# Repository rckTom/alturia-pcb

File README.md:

# Alturia PCB

This repository contains all data to build the hardware of the Alturia rocket flight computer. 

## Features
-  STM32F303CC CPU (48Kb Ram, 256Kb internal Flash)
-  MS5607 Barometric pressure sensor
-  BMI088 IMU (Acceleration: +-24g, rotational rate: +-2000°/s)
-  AIS2120SXTR high acceleration sensor (+-120g)
-  64 Megabyte external flash for logging and configuration data
-  Reverse polarity protection
-  4 x Pyro output channels with max 25A current
-  2 x PWM connector for servos
-  USB (CDC-ACM, Mass Storage and DFU)

## Getting Started

The board is built with [Kicad](http://kicad.org/). Version 5.2 or newer is required. The firmware is located at [alturia-firmware](https://github.com/rckTom/alturia-firmware)

## Board Versions
*   v1.0 rev.B *Initial Board Design*
*   v1.1 rev.A *Fix wrongly connected Crystal*
*   v1.1 rev.B *Fix swaped Pins of the speaker mosfet*

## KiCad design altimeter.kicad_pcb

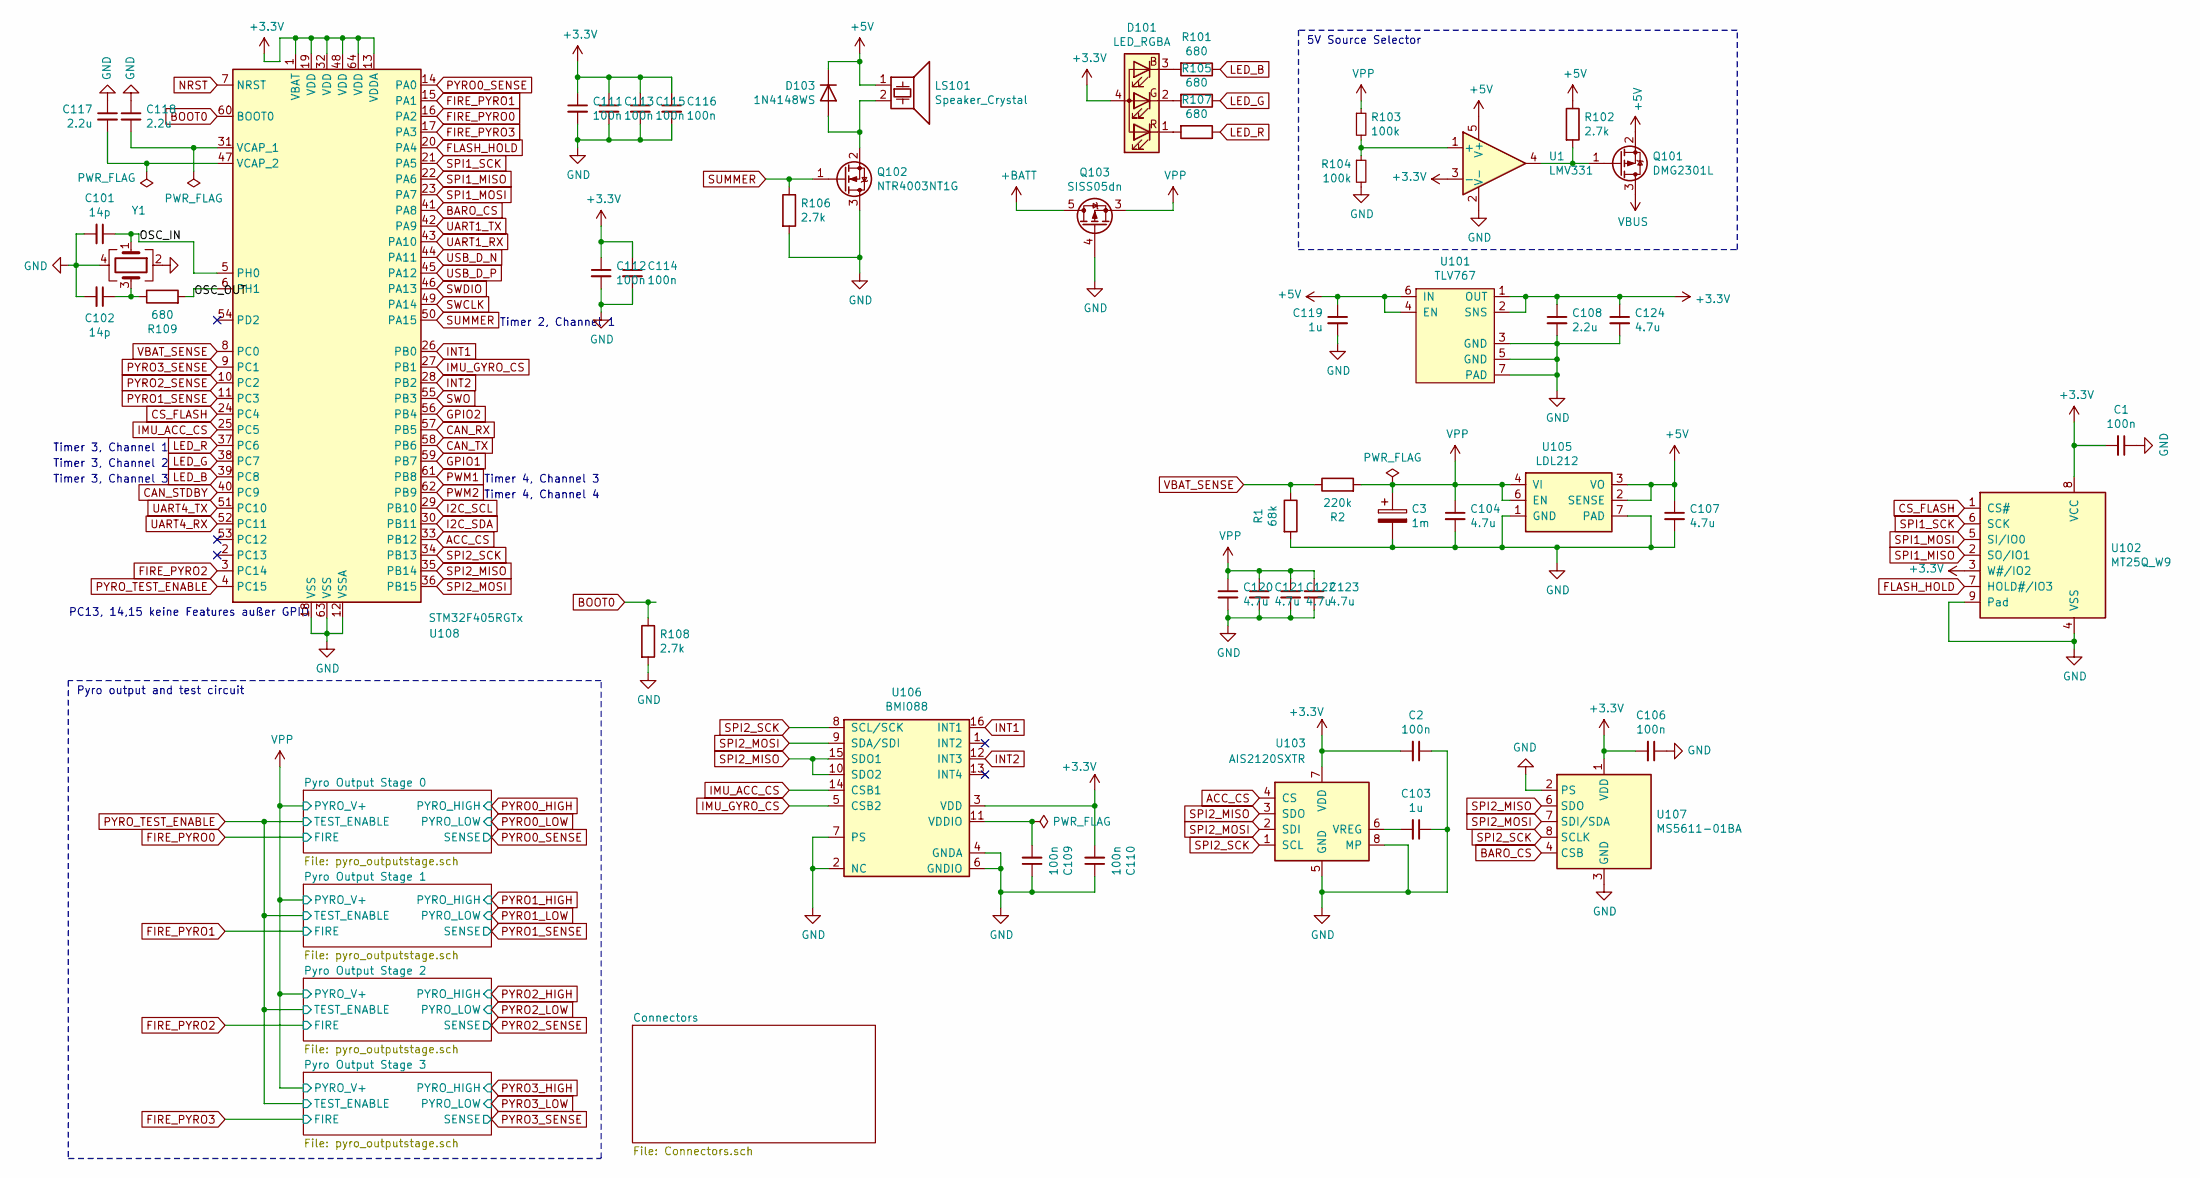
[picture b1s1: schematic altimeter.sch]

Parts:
C1, C2, C106, C109, C110, C111, C112, C113, C114, C115, C116: 100n; C_0402_1005Metric
C3: 1m; CP_Axial_L11.0mm_D8.0mm_P15.00mm_Horizontal
C101, C102: 14p; C_0402_1005Metric
C103: 1u; C_0603_1608Metric_Pad1.05x0.95mm_HandSolder
C104, C120, C121, C122, C123: 4.7u; C_0805_2012Metric_Pad1.15x1.40mm_HandSolder
C107: 4.7u; C_0805_2012Metric
C108: 2.2u; C_0603_1608Metric_Pad1.05x0.95mm_HandSolder
C117, C118: 2.2u; C_0402_1005Metric
C119: 1u; C_0805_2012Metric
C124: 4.7u; C_0603_1608Metric_Pad1.05x0.95mm_HandSolder
D101: LED_RGBA; SMD_RGB_LED
D103: 1N4148WS; D_SOD-323
LS101: Speaker_Crystal; CSS-95B30-SMT
Q101: DMG2301L; SOT-23
Q102: NTR4003NT1G; SOT-23
Q103: SISS05dn; Vishay_PowerPAK_1212-8_Single
R1: 68k; R_0402_1005Metric
R2: 220k; R_0402_1005Metric
R101, R105, R107, R109: 680; R_0402_1005Metric
R102, R106, R108: 2.7k; R_0402_1005Metric
R103, R104: 100k; R_0402_1005Metric
U1: LMV331; SOT-353_SC-70-5
U101: TLV767; TI_WSON_TLV767
U102: MT25Q_W9; micron-wpdfn_8x6mm
U103: AIS2120SXTR; SOIC-8_3.9x4.9mm_P1.27mm
U105: LDL212; DFN-6-1EP_3x3mm_P0.95mm_EP1.7x2.6mm
U106: BMI088
U107: MS5611-01BA; LGA-8_3x5mm_P1.25mm
U108: STM32F405RGTx; LQFP-64_10x10mm_P0.5mm
Y1: Crystal_GND24; Crystal_SMD_2016-4Pin_2.0x1.6mm

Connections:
+3V3: C1.2, C2.2, C106.2, C108.1, C110.2, C111.1, C112.1, C113.1, C114.1, C115.1, C116.1, C124.1, D101.4 (A), U1.3 (-), U101.1 (OUT), U101.2 (SNS), U102.3 (W#/IO2), U102.8 (VCC), U103.7 (VDD), U106.3 (VDD), U107.1 (VDD), U108.1 (VBAT), U108.13 (VDDA), U108.19 (VDD), U108.32 (VDD), U108.48 (VDD), U108.64 (VDD); also elsewhere on the board
+5V: C107.1, C119.1, D103.1 (K), LS101.1, Q101.2 (S), R102.1, U1.5 (V+), U101.4 (EN), U101.6 (IN), U105.2 (SENSE), U105.3 (VO); also elsewhere on the board
+BATT: Q103.5 (D); also elsewhere on the board
/OSC_IN: C101.1, U108.5 (PH0), Y1.1
/OSC_OUT: R109.2, U108.6 (PH1)
ACC_CS: U103.4 (CS), U108.33 (PB12)
BARO_CS: U107.4 (CSB), U107.5 (CSB), U108.41 (PA8)
BOOT0: R108.1, U108.60 (BOOT0)
CAN_RX: U108.57 (PB5); also elsewhere on the board
CAN_STDBY: U108.40 (PC9); also elsewhere on the board
CAN_TX: U108.58 (PB6); also elsewhere on the board
CS_FLASH: U102.1 (CS#), U108.24 (PC4)
FIRE_PYRO2: U108.3 (PC14); also elsewhere on the board
FIRE_PYRO3: U108.17 (PA3); also elsewhere on the board
FLASH_HOLD: U102.7 (HOLD#/IO3), U108.20 (PA4)
GND: C1.1, C2.1, C3.2, C101.2, C102.2, C103.1, C104.2, C106.1, C107.2, C108.2, C109.1, C110.1, C111.2, C112.2, C113.2, C114.2, C115.2, C116.2, C117.1, C118.1, C119.2, C120.2, C121.2, C122.2, C123.2, C124.2, Q102.3 (D), Q103.4 (G), R1.2, R104.2, R106.2, R108.2, U1.2 (V-), U101.3 (GND), U101.5 (GND), U101.7 (PAD), U102.4 (VSS), U102.9 (Pad), U103.5 (GND), U103.8 (MP), U105.1 (GND), U105.7 (PAD), U106.2 (NC), U106.4 (GNDA), U106.6 (GNDIO), U106.7 (PS), U107.2 (PS), U107.3 (GND), U108.12 (VSSA), U108.18 (VSS), U108.63 (VSS), Y1.2, Y1.4; also elsewhere on the board
GPIO1: U108.59 (PB7); also elsewhere on the board
GPIO2: U108.56 (PB4); also elsewhere on the board
I2C_SCL: U108.29 (PB10); also elsewhere on the board
I2C_SDA: U108.30 (PB11); also elsewhere on the board
IMU_ACC_CS: U106.14 (CSB1), U108.25 (PC5)
IMU_GYRO_CS: U106.5 (CSB2), U108.27 (PB1)
INT1: U106.16 (INT1), U108.26 (PB0)
INT2: U106.12 (INT3), U108.28 (PB2)
LED_B: R101.1, U108.39 (PC8)
LED_G: R105.1, U108.38 (PC7)
LED_R: R107.1, U108.37 (PC6)
NRST: U108.7 (NRST); also elsewhere on the board
unnamed: C102.1, R109.1, Y1.3
unnamed: C103.2, U103.6 (VREG)
unnamed: C109.2, U106.11 (VDDIO)
unnamed: C117.2, U108.47 (VCAP_2)
unnamed: C118.2, U108.31 (VCAP_1)
unnamed: D101.1 (RK), R107.2
unnamed: D101.2 (GK), R105.2
unnamed: D101.3 (BK), R101.2
unnamed: D103.2 (A), LS101.2, Q102.2 (S)
unnamed: Q101.1 (G), R102.2, U1.4
unnamed: R103.2, R104.1, U1.1 (+)
PWM1: U108.61 (PB8); also elsewhere on the board
PWM2: U108.62 (PB9); also elsewhere on the board
PYRO0_SENSE: U108.14 (PA0); also elsewhere on the board
PYRO1_SENSE: U108.11 (PC3); also elsewhere on the board
PYRO2_SENSE: U108.10 (PC2); also elsewhere on the board
PYRO3_SENSE: U108.9 (PC1); also elsewhere on the board
PYRO_TEST_ENABLE: U108.4 (PC15); also elsewhere on the board
SPI1_MISO: U102.2 (SO/IO1), U108.22 (PA6)
SPI1_MOSI: U102.5 (SI/IO0), U108.23 (PA7)
SPI1_SCK: U102.6 (SCK), U108.21 (PA5)
SPI2_MISO: U103.3 (SDO), U106.10 (SDO2), U106.15 (SDO1), U107.6 (SDO), U108.35 (PB14)
SPI2_MOSI: U103.2 (SDI), U106.9 (SDA/SDI), U107.7 (SDI/SDA), U108.36 (PB15)
SPI2_SCK: U103.1 (SCL), U106.8 (SCL/SCK), U107.8 (SCLK), U108.34 (PB13)
SUMMER: Q102.1 (G), R106.1, U108.50 (PA15)
SWCLK: U108.49 (PA14); also elsewhere on the board
SWDIO: U108.46 (PA13); also elsewhere on the board
SWO: U108.55 (PB3); also elsewhere on the board
UART1_RX: U108.43 (PA10); also elsewhere on the board
UART1_TX: U108.42 (PA9); also elsewhere on the board
UART4_RX: U108.52 (PC11); also elsewhere on the board
UART4_TX: U108.51 (PC10); also elsewhere on the board
USB_D_N: U108.44 (PA11); also elsewhere on the board
USB_D_P: U108.45 (PA12); also elsewhere on the board
VBAT_SENSE: R1.1, R2.1, U108.8 (PC0)
VBUS: Q101.3 (D); also elsewhere on the board

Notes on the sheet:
Pyro output and test circuit
5V Source Selector
Timer 4, Channel 4
Timer 4, Channel 3
Timer 3, Channel 1
Timer 3, Channel 2
Timer 3, Channel 3
Timer 2, Channel 1
PC13, 14,15 keine Features außer GPIO

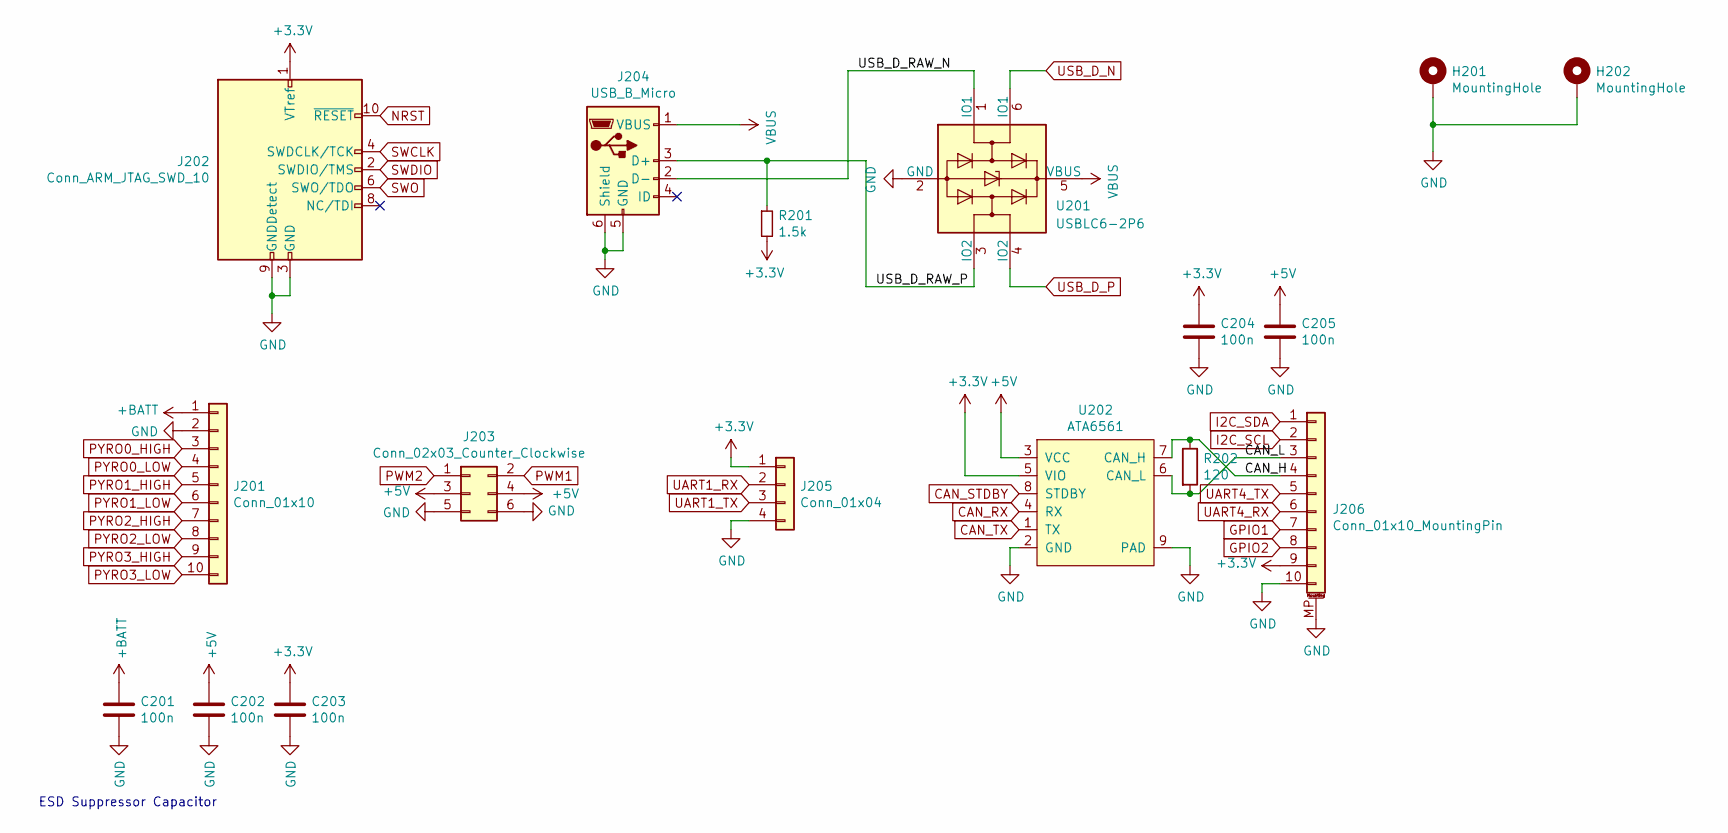
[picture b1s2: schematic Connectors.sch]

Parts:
C201, C202, C203, C204, C205: 100n; C_0402_1005Metric
H201, H202: MountingHole; MountingHole_3.2mm_M3_Pad_Via
J201: Conn_01x10; Molex_MicroClasp_55935-1010_1x10_P2.00mm_Horizontal
J202: Conn_ARM_JTAG_SWD_10; PinHeader_2x05_P2.00mm_Vertical_SMD
J203: Conn_02x03_Counter_Clockwise; PinHeader_2x03_P2.54mm_Horizontal
J204: USB_B_Micro; USB_Micro-B_Molex-105017-0001
J205: Conn_01x04; Molex_PicoBlade_53048-0410_1x04_P1.25mm_Horizontal
J206: Conn_01x10_MountingPin; Molex_PicoBlade_53398-1071_1x10-1MP_P1.25mm_Vertical
R201: 1.5k; R_0402_1005Metric
R202: 120; R_0603_1608Metric_Pad1.05x0.95mm_HandSolder
U201: USBLC6-2P6; SOT-666
U202: ATA6561; DFN-8-1EP_3x3mm_P0.65mm_EP1.55x2.4mm

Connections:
+3V3: C203.1, C204.1, J202.1 (VTref), J205.1, J206.9, R201.2, U202.5 (VIO); also elsewhere on the board
+5V: C202.1, C205.1, J203.3, J203.4, U202.3 (VCC); also elsewhere on the board
+BATT: C201.1, J201.1; also elsewhere on the board
/Connectors/CAN_H: J206.4, R202.1, U202.7 (CAN_H)
/Connectors/CAN_L: J206.3, R202.2, U202.6 (CAN_L)
/Connectors/USB_D_RAW_N: J204.2 (D-), U201.1 (IO1)
/Connectors/USB_D_RAW_P: J204.3 (D+), R201.1, U201.3 (IO2)
CAN_RX: U202.4 (RX); also elsewhere on the board
CAN_STDBY: U202.8 (STDBY); also elsewhere on the board
CAN_TX: U202.1 (TX); also elsewhere on the board
GND: C201.2, C202.2, C203.2, C204.2, C205.2, H201.1, H202.1, J201.2, J202.3 (GND), J202.5 (GND), J202.9 (GNDDetect), J203.5, J203.6, J204.5 (GND), J204.6 (Shield), J205.4, J206.10, J206.MP (MountPin), U201.2 (GND), U202.2 (GND), U202.9 (PAD); also elsewhere on the board
GPIO1: J206.7; also elsewhere on the board
GPIO2: J206.8; also elsewhere on the board
I2C_SCL: J206.2; also elsewhere on the board
I2C_SDA: J206.1; also elsewhere on the board
NRST: J202.10 (~RESET~); also elsewhere on the board
PWM1: J203.2; also elsewhere on the board
PWM2: J203.1; also elsewhere on the board
PYRO2_LOW: J201.8; also elsewhere on the board
PYRO3_LOW: J201.10; also elsewhere on the board
SWCLK: J202.4 (SWDCLK/TCK); also elsewhere on the board
SWDIO: J202.2 (SWDIO/TMS); also elsewhere on the board
SWO: J202.6 (SWO/TDO); also elsewhere on the board
UART1_RX: J205.2; also elsewhere on the board
UART1_TX: J205.3; also elsewhere on the board
UART4_RX: J206.6; also elsewhere on the board
UART4_TX: J206.5; also elsewhere on the board
USB_D_N: U201.6 (IO1); also elsewhere on the board
USB_D_P: U201.4 (IO2); also elsewhere on the board
VBUS: J204.1 (VBUS), U201.5 (VBUS); also elsewhere on the board

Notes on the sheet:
ESD Suppressor Capacitor

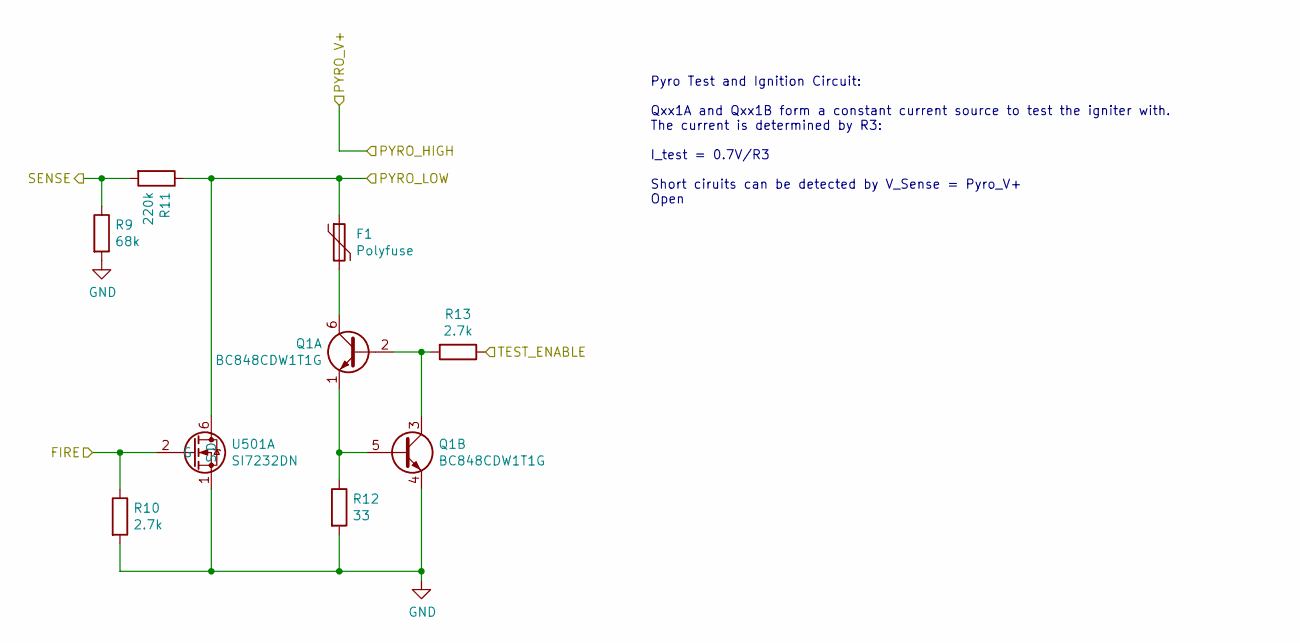
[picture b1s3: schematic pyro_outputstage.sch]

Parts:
F301: Polyfuse; Fuse_0603_1608Metric_Pad1.05x0.95mm_HandSolder
Q301: BC848CDW1T1G; SOT-363_SC-70-6
R3: 68k; R_0402_1005Metric
R4: 220k; R_0402_1005Metric
R301, R303: 2.7k; R_0402_1005Metric
R302: 33; R_0402_1005Metric
U301: SI7232DN; Vishay_PowerPAK_1212-8_Dual

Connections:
GND: Q301.4 (E2), R3.2, R301.2, R302.2, U301.1 (S), U301.3 (S); also elsewhere on the board
unnamed: F301.2, Q301.6 (C1)
unnamed: Q301.1 (E1), Q301.5 (B2), R302.1
unnamed: Q301.2 (B1), Q301.3 (C2), R303.2
PYRO0_SENSE: R3.1, R4.2; also elsewhere on the board
PYRO_TEST_ENABLE: R303.1; also elsewhere on the board

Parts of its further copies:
F1, F401, F501: Polyfuse; Fuse_0603_1608Metric_Pad1.05x0.95mm_HandSolder
Q1, Q401, Q501: BC848CDW1T1G; SOT-363_SC-70-6
R5, R7, R9: 68k; R_0402_1005Metric
R6, R8, R11: 220k; R_0402_1005Metric
R10, R13, R401, R403, R501, R503: 2.7k; R_0402_1005Metric
R12, R402, R502: 33; R_0402_1005Metric
U501: SI7232DN; Vishay_PowerPAK_1212-8_Dual

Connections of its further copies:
FIRE_PYRO2: R501.1, U501.4 (G); also elsewhere on the board
FIRE_PYRO3: R10.1, U501.2 (G); also elsewhere on the board
GND: Q1.4 (E2), Q401.4 (E2), Q501.4 (E2), R5.2, R7.2, R9.2, R10.2, R12.2, R401.2, R402.2, R501.2, R502.2, U501.1 (S), U501.3 (S); also elsewhere on the board
unnamed: F1.2, Q1.6 (C1)
unnamed: F401.2, Q401.6 (C1)
unnamed: F501.2, Q501.6 (C1)
unnamed: Q1.1 (E1), Q1.5 (B2), R12.1
unnamed: Q1.2 (B1), Q1.3 (C2), R13.2
unnamed: Q401.1 (E1), Q401.5 (B2), R402.1
unnamed: Q401.2 (B1), Q401.3 (C2), R403.2
unnamed: Q501.1 (E1), Q501.5 (B2), R502.1
unnamed: Q501.2 (B1), Q501.3 (C2), R503.2
PYRO1_SENSE: R5.1, R6.2; also elsewhere on the board
PYRO2_LOW: F501.1, R8.1, U501.5 (D); also elsewhere on the board
PYRO2_SENSE: R7.1, R8.2; also elsewhere on the board
PYRO3_LOW: F1.1, R11.1, U501.6 (D); also elsewhere on the board
PYRO3_SENSE: R9.1, R11.2; also elsewhere on the board
PYRO_TEST_ENABLE: R13.1, R403.1, R503.1; also elsewhere on the board

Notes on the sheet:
Pyro Test and Ignition Circuit: Qxx1A and Qxx1B form a constant current source to test the igniter with. The current is determined by R3: I_test = 0.7V/R3 Short ciruits can be detected by V_Sense = Pyro_V+ Open

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
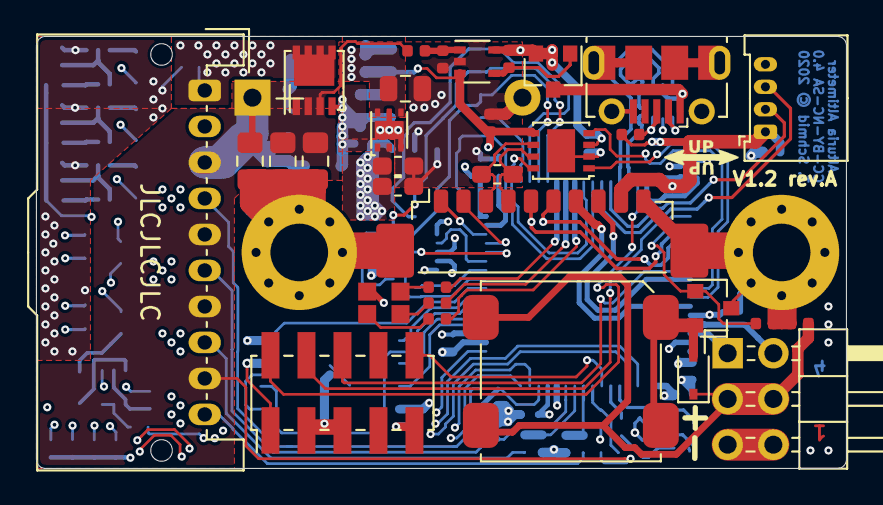
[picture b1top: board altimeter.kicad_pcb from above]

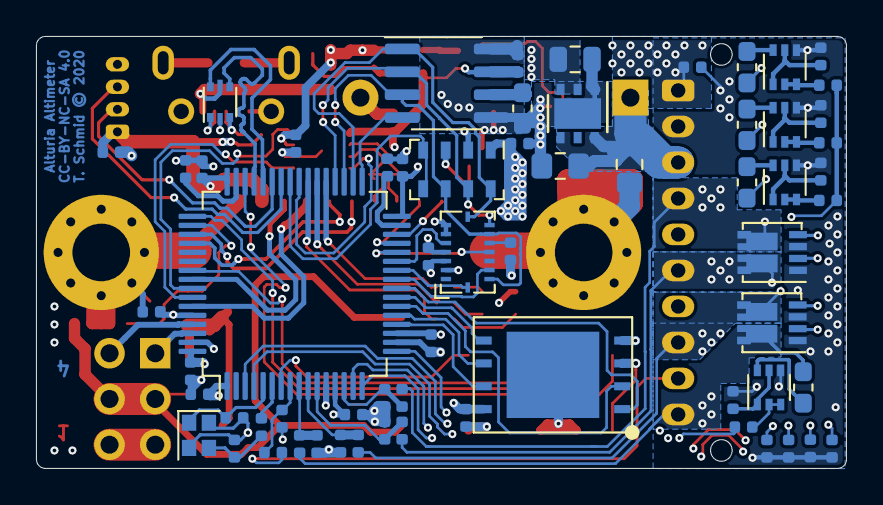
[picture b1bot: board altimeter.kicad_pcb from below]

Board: 4 copper layers, 45.0 x 24.0 mm, 100 parts (64 on the bottom side), 87 nets.

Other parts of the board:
Ref**: up_arrow

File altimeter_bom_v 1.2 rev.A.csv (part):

Component,Description,Part,References,Value,Footprint,Quantity Per PCB,Datasheet,Mouser_Link,Parnumber
1,"Unpolarized capacitor, small symbol",C_Small,C1 C2 C106 C109 C110 C111 C112 C113 C114 C115 C116 C201 C202 C203 C204 C205,100n,C_0402_1005Metric,16,~,https://www.mouser.de/ProductDetail/Wurth-Elektronik/8850122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,885012205037
2,"Unpolarized capacitor, small symbol",C_Small,C101 C102,14p,C_0402_1005Metric,2,~,https://www.mouser.de/ProductDetail/Murata-Electronics/GCM15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,GCM1555G1H220JA16D
3,Polarized capacitor,CP,C3,1m,CP_Axial_L11.0mm_D8.0mm_P15.00mm_Horizontal,1,~,https://www.mouser.de/ProductDetail/Illinois-Capacitor-CDE/3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,337TTA016M
4,"Unpolarized capacitor, small symbol",C_Small,C103,1u,C_0603_1608Metric_Pad1.05x0.95mm_HandSolder,1,~,https://www.mouser.de/ProductDetail/Yageo/CC0603KRX5R8BB105?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,CC0603KRX5R8BB105
5,"Unpolarized capacitor, small symbol",C_Small,C119,1u,C_0805_2012Metric,1,~,https://www.mouser.de/ProductDetail/Taiyo-Yuden/EMK107BJ225M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,EMK107BJ225MA-T
6,"Unpolarized capacitor, small symbol",C_Small,C108,2.2u,C_0603_1608Metric_Pad1.05x0.95mm_HandSolder,1,~,https://www.mouser.de/ProductDetail/Taiyo-Yuden/EMK107ABJ475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,EMK107ABJ475KA-T
7,"Unpolarized capacitor, small symbol",C_Small,C117 C118,2.2u,C_0402_1005Metric,2,~,https://www.mouser.de/ProductDetail/Wurth-Elektronik/8850122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,885012205037
8,"Unpolarized capacitor, small symbol",C_Small,C104 C120 C121 C122 C123,4.7u,C_0805_2012Metric_Pad1.15x1.40mm_HandSolder,5,~,https://www.mouser.de/ProductDetail/KEMET/C0805C104Z3VACTU?q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,C0805C104Z3VACTU
9,"Unpolarized capacitor, small symbol",C_Small,C107,4.7u,C_0805_2012Metric,1,~,https://www.mouser.de/ProductDetail/Taiyo-Yuden/EMK107BJ225M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,EMK107BJ225MA-T
10,"Unpolarized capacitor, small symbol",C_Small,C124,4.7u,C_0603_1608Metric_Pad1.05x0.95mm_HandSolder,1,~,https://www.mouser.de/ProductDetail/Taiyo-Yuden/EMK107ABJ475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,EMK107ABJ475KA-T
11,"75V 0.15A Fast switching Diode, SOD-323",1N4148WS,D103,1N4148WS,D_SOD-323,1,https://www.vishay.com/docs/85751/1n4148ws.pdf,https://www.mouser.de/ProductDetail/ON-Semiconductor-Fairchi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,1N4148WS
12,"RGB LED, red/green/blue/anode",LED_RGBA,D101,LED_RGBA,SMD_RGB_LED,1,https://www.mouser.de/datasheet/2/445/150080M153000-1714255.pdf,https://www.mouser.de/ProductDetail/Wurth-Elektronik/150080M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,150080M153000
13,"Resettable fuse, polymeric positive temperature coefficient",Polyfuse,F1 F301 F401 F501,Polyfuse,Fuse_0603_1608Metric_Pad1.05x0.95mm_HandSolder,4,~,https://www.mouser.de/ProductDetail/Bel-Fuse/0ZCM0008FF2G?qs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,0ZCM0008FF2G
14,"Generic connector, single row, 01x04, script generated (kicad-library-utils/schlib/autogen/connector/)",Conn_01x04,J205,Conn_01x04,Molex_PicoBlade_53048-0410_1x04_P1.25mm_Horizontal,1,~,https://www.mouser.de/ProductDetail/Molex/53048-0410?qs=%2Fh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,53048-0410
15,"Generic connector, single row, 01x10, script generated (kicad-library-utils/schlib/autogen/connector/)",Conn_01x10,J201,Conn_01x10,Molex_MicroClasp_55935-1010_1x10_P2.00mm_Horizontal,1,~,https://www.mouser.de/ProductDetail/Molex/55935-1010?qs=%2Fh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,55935-1010
16,"Generic connectable mounting pin connector, single row, 01x10, script generated (kicad-library-utils/schlib/autogen/connector/)",Conn_01x10_MountingPin,J206,Conn_01x10_MountingPin,Molex_PicoBlade_53398-1071_1x10-1MP_P1.25mm_Vertical,1,~,https://www.mouser.de/ProductDetail/Molex/53398-1071?qs=%2Fh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,53398-1071
17,"Generic connector, double row, 02x03, odd/even pin numbering scheme (row 1 odd numbers, row 2 even numbers), script generated (kicad-library-utils/schlib/autogen/connector/)",Conn_02x03_Odd_Even,J203,Conn_02x03_Counter_Clockwise,PinHeader_2x03_P2.54mm_Horizontal,1,~,https://www.mouser.de/ProductDetail/Harwin/M20-9740346?qs=sG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,M20-9740346
18,"Cortex Debug Connector, standard ARM Cortex-M SWD and JTAG interface",Conn_ARM_JTAG_SWD_10,J202,Conn_ARM_JTAG_SWD_10,PinHeader_2x05_P2.00mm_Vertical_SMD,1,http://infocenter.arm.com/help/topic/com.arm.doc.ddi0314h/DD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,https://www.mouser.de/ProductDetail/Amphenol-FCI/57202-G51-0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,57202-G51-05LF
19,USB Micro Type B connector,USB_B_Micro,J204,USB_B_Micro,USB_Micro-B_Molex-105017-0001,1,~,https://www.mouser.de/ProductDetail/Molex/105017-0001?qs=sGA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,105017-0001
20,Crystal speaker/transducer,Speaker_Crystal,LS101,Speaker_Crystal,CSS-95B30-SMT,1,https://www.mouser.de/datasheet/2/670/css-95b30-smt-1311901.pdf,https://www.mouser.de/ProductDetail/CUI/CSS-95B30-SMT-TR?qs=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,CSS-95B30-SMT-TR
21,"100mA IC, 45V Vce, Dual NPN/NPN Transistors, SOT-363",BC847BDW1,Q1 Q301 Q401 Q501,BC848CDW1T1G,SOT-363_SC-70-6,4,http://www.onsemi.com/pub_link/Collateral/BC846BDW1T1-D.PDF,https://www.mouser.de/manufacturer/on-semiconductor/,BC848CDW1T1G
22,"P-MOSFET transistor, gate/source/drain",Q_PMOS_GSD,Q101,DMG2301L,SOT-23,1,~,https://www.mouser.de/ProductDetail/Diodes-Incorporated/DMG2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,DMG2301L-7
23,"N-MOSFET transistor, gate/source/drain",Q_NMOS_GSD,Q102,NTR4003NT1G,SOT-23,1,~,https://www.mouser.de/ProductDetail/ON-Semiconductor/NTR4003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,NTR4003NT1G
24,"P-MOSFET transistor, drain/gate/source",SI7149ADP,Q103,SISS05dn,Vishay_PowerPAK_1212-8_Single,1,https://www.mouser.de/datasheet/2/427/siss05dn-1595673.pdf,https://www.mouser.de/ProductDetail/Vishay-Siliconix/SISS05D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,SISS05DN-T1-GE3
25,"Resistor, small symbol",R_Small,R201,1.5k,R_0402_1005Metric,1,~,https://www.mouser.de/ProductDetail/Vishay-Dale/CRCW04021K50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,CRCW04021K50FKEDC
26,"Resistor, small symbol",R_Small,R103 R104,100k,R_0402_1005Metric,2,~,https://www.mouser.de/ProductDetail/Vishay-Dale/CRCW0402100K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,CRCW0402100KFKEDC
27,Resistor,R,R202,120,R_0603_1608Metric_Pad1.05x0.95mm_HandSolder,1,~,https://www.mouser.de/datasheet/2/315/AOA0000C304-1149620.pdf,ERJ-6RBD1200V
28,Resistor,R,R10 R13 R102 R106 R108 R301 R303 R401 R403 R501 R503,2.7k,R_0402_1005Metric,11,~,https://www.mouser.de/ProductDetail/Vishay-Dale/CRCW04022K70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,CRCW04022K70FKEDC
29,Resistor,R,R2 R4 R6 R8 R11,220k,R_0402_1005Metric,5,~,https://www.mouser.de/ProductDetail/Vishay-Dale/CRCW0402220K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,CRCW0402220KFKEDC
30,Resistor,R,R12 R302 R402 R502,33,R_0402_1005Metric,4,~,https://www.mouser.de/ProductDetail/TE-Connectivity-Neohm/CP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,CPF0402B33RE1
31,Resistor,R,R101 R105 R107 R109,680,R_0402_1005Metric,4,~,https://www.mouser.de/ProductDetail/Vishay-Dale/CRCW0402680R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,CRCW0402680RFKEDC
32,Resistor,R,R1 R3 R5 R7 R9,68k,R_0402_1005Metric,5,~,https://www.mouser.de/ProductDetail/Vishay-Dale/CRCW0402768K0FKEDC,CRCW040268K0FKEDC
33,,AIS2120SXTR,U103,AIS2120SXTR,SOIC-8_3.9x4.9mm_P1.27mm,1,,https://www.mouser.de/ProductDetail/STMicroelectronics/AIS21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,AIS2120SXTR
34,,ATA6561,U202,ATA6561,DFN-8-1EP_3x3mm_P0.65mm_EP1.55x2.4mm,1,http://ww1.microchip.com/downloads/en/DeviceDoc/20005991B.pdf,https://www.mouser.de/ProductDetail/Microchip-Technology/ATA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,ATA6561-GBQW-N
35,,BMI088,U106,BMI088,BMI088,1,,https://www.mouser.de/ProductDetail/Bosch-Sensortec/BMI088?q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,BMI088
36,,LDL212,U105,LDL212,DFN-6-1EP_3x3mm_P0.95mm_EP1.7x2.6mm,1,https://www.st.com/resource/en/datasheet/ldl212.pdf,https://www.mouser.de/ProductDetail/STMicroelectronics/LDL21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,LDL212PU50R
37,"Single General-Purpose Low-Voltage Comparator, SOT-23-5/SC-70-5",LMV331,U1,LMV331,SOT-353_SC-70-5,1,http://www.ti.com/lit/ds/symlink/lmv331.pdf,https://www.mouser.de/datasheet/2/115/LMV331_393-335820.pdf,LMV331SE-7
38,"Barometric pressure sensor, 10cm resolution, 10 to 1200 mbar, I2C and SPI interface up to 20MHz, LGA-8",MS5611-01BA,U107,MS5611-01BA,LGA-8_3x5mm_P1.25mm,1,https://www.te.com/commerce/DocumentDelivery/DDEController?A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,https://www.mouser.de/ProductDetail/Measurement-Specialties/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,MS560702BA03-50
39,,MT25Q_W9,U102,MT25Q_W9,micron-wpdfn_8x6mm,1,https://www.micron.com/-/media/client/global/documents/produ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,https://www.mouser.de/ProductDetail/Micron/MT25QL512ABB1EW9-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,MT25QL512ABB1EW9-0SIT
40,,SI7232DN,U301 U501,SI7232DN,Vishay_PowerPAK_1212-8_Dual,2,,https://www.mouser.de/ProductDetail/Vishay-Siliconix/SI7232D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,SI7232DN-T1-GE3
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
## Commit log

2019-07-28 updates to schematic
2019-07-29 add pyro output stages
2019-07-29 increate outline linewidth to conform with the kicad library convention
2019-08-01 update pyro output stage. add a fuse to the test circuit and remove pullup for sense line
2019-08-07 add gitignore and delete some unnecessary files
2019-08-07 more work on schematic and layout
2019-08-08 update to schematic and layout
2019-08-09 flash considerations
2019-08-11 major work on layout. nearly finished
2019-08-14 nearly finished with lacout. Added logo
2019-08-14 add cc-by-nc-sa 4.0 license
2019-09-04 completed layout
2019-09-04 minor updates
2019-09-04 first prototyp order
2019-09-05 fix untinted vias
2019-09-06 add some missing mouser links and part numbers to the schematic
2019-09-06 changed mcu from stm32f302xc to stm32f303xc
2019-09-06 add missing 3d model for bmi088
2019-09-23 add readme
2019-09-26 fix wrong connection of quarz
2019-11-06 swap net names for bmi088 chip select lines
2019-11-21 with kicad 5.1.5 the required molex connector is part of the kicad footprint library. Remove custom molex footprints link
2020-01-30 readme: fix some wrong numbers
2020-05-12 fix swaped gate and source pin of pyro mosfets
2020-05-12 fix servo connectors
    fix pinout of servo connectors. 5V Pin and Signal was swapped
2020-06-28 v1.2 rev A
2021-11-10 Update README.md
    https://forum.kicad.info/t/warning-avoid-all-links-to-kicad-pcb-org-use-kicad-org/31521

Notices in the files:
altimeter.kicad_pcb:
T. Schmid © 2020
